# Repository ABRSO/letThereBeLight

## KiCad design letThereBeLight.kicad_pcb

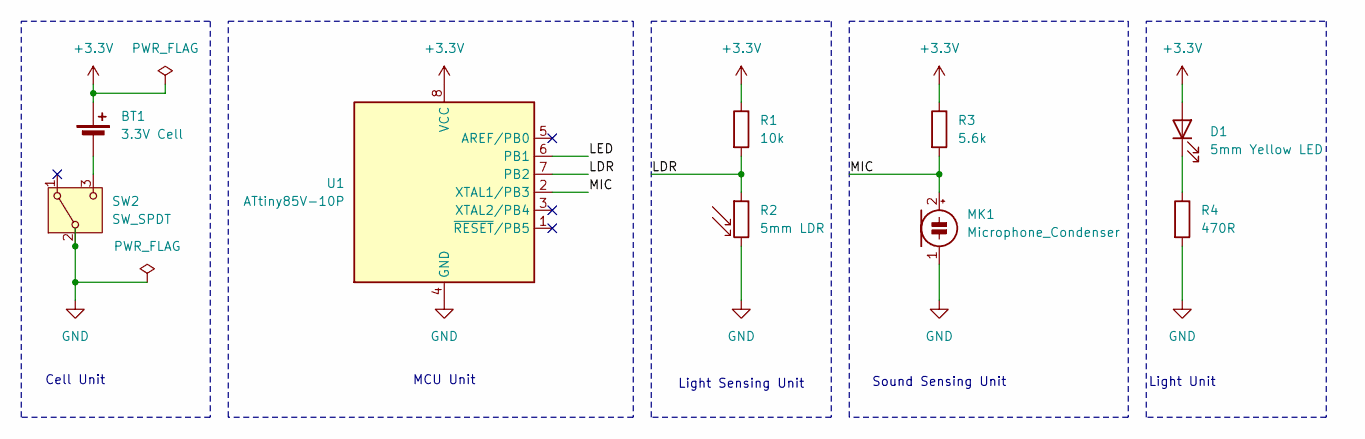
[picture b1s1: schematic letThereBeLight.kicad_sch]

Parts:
BT1: 3.3V Cell; BatteryHolder_ComfortableElectronic_CH273-2450_1x2450
D1: 5mm Yellow LED; LED_D5.0mm
MK1: Microphone_Condenser; PinHeader_1x02_P2.54mm_Vertical
R1: 10k; R_Axial_DIN0207_L6.3mm_D2.5mm_P15.24mm_Horizontal
R2: 5mm LDR; R_LDR_5.1x4.3mm_P3.4mm_Vertical
R3: 5.6k; R_Axial_DIN0207_L6.3mm_D2.5mm_P15.24mm_Horizontal
R4: 470R; R_Axial_DIN0207_L6.3mm_D2.5mm_P15.24mm_Horizontal
SW2: SW_SPDT; SW_Slide_SPDT_Angled_CK_OS102011MA1Q
U1: ATtiny85V-10P; DIP-8_W7.62mm

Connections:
+3.3V: BT1.1 (+), D1.2 (A), R1.1, R3.1, U1.8 (VCC)
/LDR: R1.2, R2.1, U1.7 (PB2)
/LED: U1.6 (PB1)
/MIC: MK1.2 (+), R3.2, U1.2 (XTAL1/PB3)
GND: MK1.1 (-), R2.2, R4.2, SW2.2 (B), U1.4 (GND)
unnamed: BT1.2 (-), SW2.3 (C)
unnamed: D1.1 (K), R4.1

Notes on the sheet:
Cell Unit
Sound Sensing Unit
Light Unit
Light Sensing Unit
MCU Unit

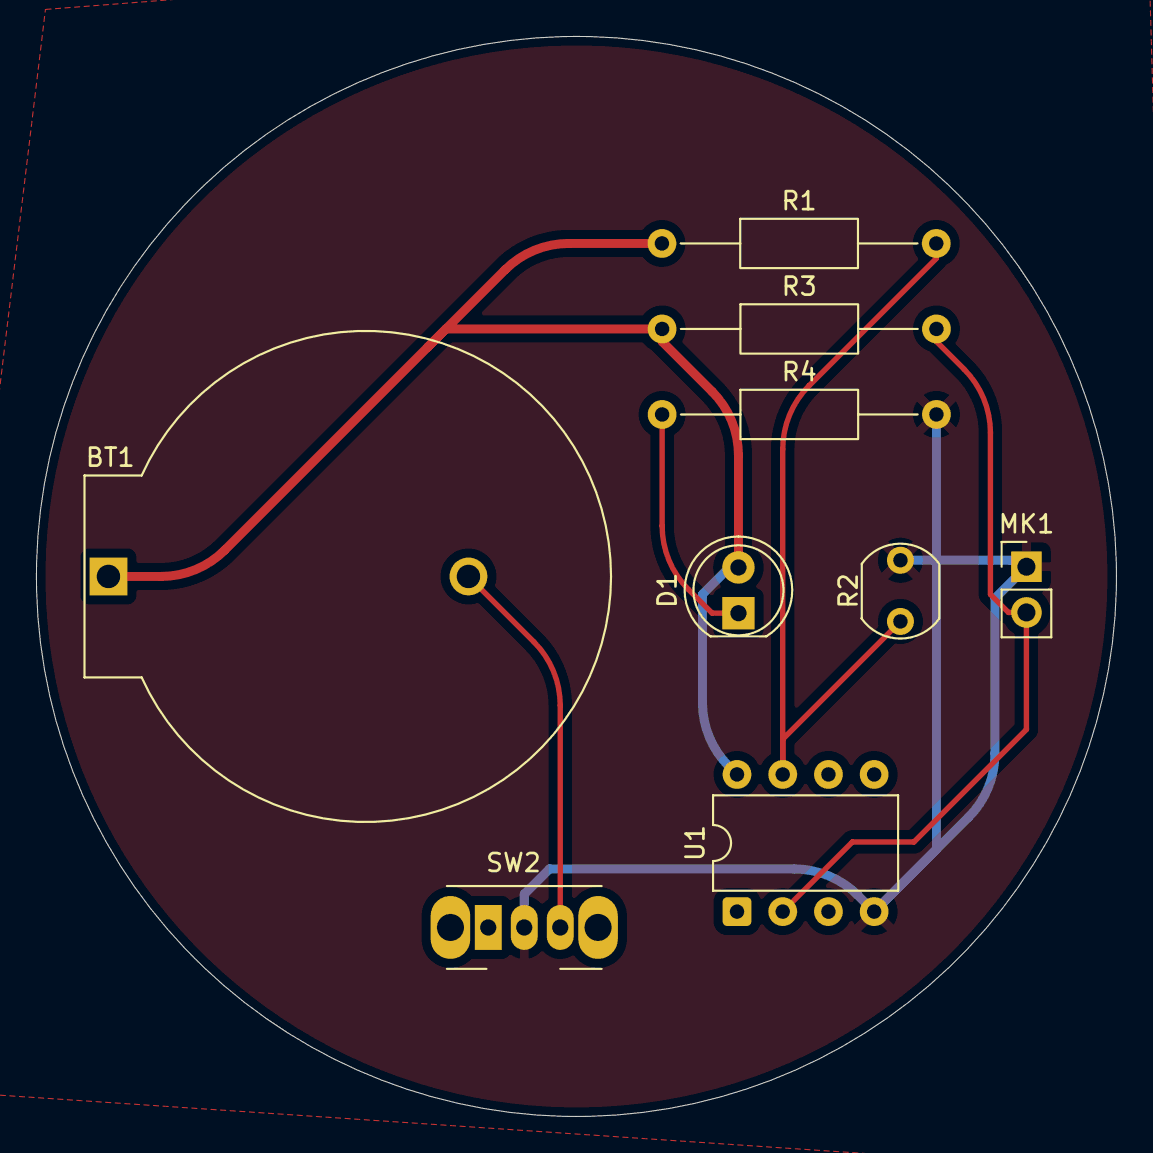
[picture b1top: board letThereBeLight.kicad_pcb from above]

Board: 2 copper layers, 60.0 x 60.0 mm, 9 parts (0 on the bottom side), 6 nets.

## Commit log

2025-07-03 create footprint
2025-07-03 configure constraints and get ready to design PCB
2025-07-04 generate gerber files
